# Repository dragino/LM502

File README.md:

# LM502 Project (Base on ASR6502 SX1262 module)
===============

Directory:
- Hardware: LM502 Demo Board Hardware Source, Design in Eagle.
- Software: LM502 Source Code.
- Release: Hex file release
- Miscellaneous: Releated stuff in examples

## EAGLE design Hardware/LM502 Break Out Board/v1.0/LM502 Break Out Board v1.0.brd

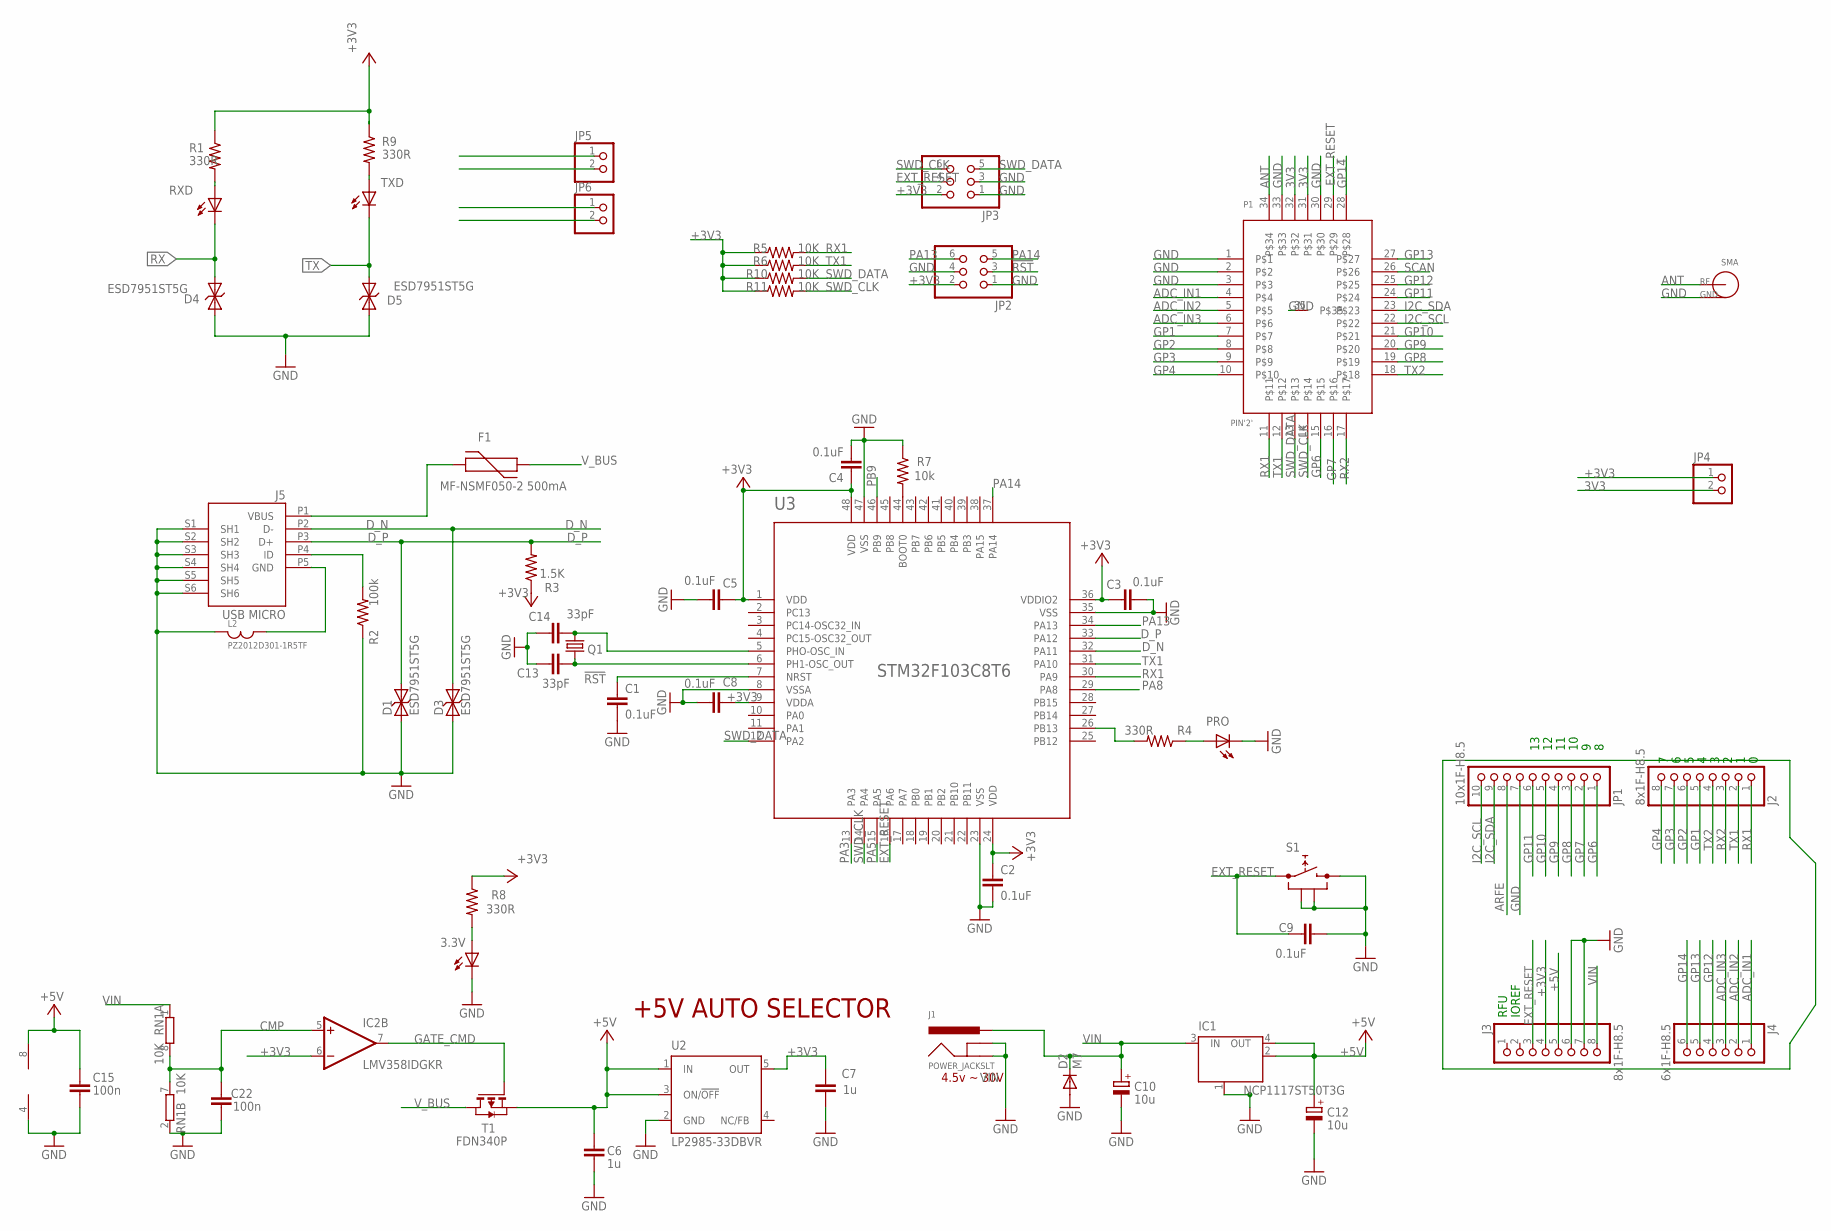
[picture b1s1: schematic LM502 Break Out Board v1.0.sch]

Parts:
3.3V: LEDCHIP-LED0603; CHIP-LED0603
C1, C2, C3, C4, C5, C8, C9: 0.1uF; C0402
C6, C7: 1u; C0603-ROUND
C10, C12: 10u; SMC_B
C13, C14: 33pF; C0402
C15, C22: 100n; C0402
D1, D3, D4, D5: ESD7951ST5G; SOD−923
D2: M7; SMB
F1: MF-NSMF050-2 500mA; R1206
IC1: NCP1117ST50T3G; SOT223
IC2: LMV358IDGKR; MSOP08
J1: POWER_JACKSLT; POWER_JACK_SLOT
J2, J3: 8x1F-H8.5; 1X08
J4: 6x1F-H8.5; 1X06
J5: USB MICRO; CON2_USB_MICRO_B_AT
JP1: 10x1F-H8.5; 1X10
JP2: PINHD-2X3; 2X3-2.0
JP3: PINHD-2X3'2'; 2X03
JP4, JP5, JP6: PINHD-1X2; 1X02
L2: PZ2012D301-1R5TF; C0805@1
P1: PIN'2'; LM502
PRO: LEDCHIP-LED0603; CHIP-LED0603
Q1: CRYSTALHC49S; HC49/S
R1, R4, R8, R9: 330R; R0402
R2: 100k; R0402
R3: 1.5K; R0402
R5, R6, R10, R11: 10K; R0402
R7: 10k; R0402
RN1: 10K; CAY16
RXD: LEDCHIP-LED0603; CHIP-LED0603
S1: PUSH_SWITCH; SWITCH_6X6X5
SMA: SMA-KWE
T1: FDN340P; SOT-23
TXD: LEDCHIP-LED0603; CHIP-LED0603
U2: LP2985-33DBVR; SOT23-DBV
U3: STM32F103C8T6; LQFP48

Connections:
3V3: JP4.2, P1.31, P1.32
!RST: C1.1, JP2.3, U3.7 (NRST)
+3V3: C2.1, C3.1, C4.1, C5.1, C7.2, C8.1, IC2.6 (-IN), J3.4, JP2.2, JP3.2, JP4.1, R1.1, R3.1, R5.1, R6.1, R8.1, R9.1, R10.1, R11.1, U2.5 (OUT), U3.1 (VDD), U3.9 (VDDA), U3.24 (VDD), U3.36 (VDDIO2), U3.48 (VDD)
+5V: C6.2, C12.+, C15.1, IC1.2 (OUT), IC1.4 (OUT), IC2.8 (V+), J3.5, T1.2 (S), U2.1 (IN), U2.3 (ON/!OFF)
ADC_IN1: J4.1, P1.4
ADC_IN2: J4.2, P1.5
ADC_IN3: J4.3, P1.6
ANT: P1.34, SMA.1 (SIG)
ARFE: JP1.8
CMP: C22.2, IC2.5 (+IN), RN1.7 (2), RN1.8 (2)
D_N: D3.P$2 (2), J5.P2 (D-), U3.32 (PA11)
D_P: D1.P$2 (2), J5.P3 (D+), R3.2, U3.33 (PA12)
EXT_RESET: C9.1, J3.3, JP3.4, P1.29, S1.1, U3.16 (PA6)
GATE_CMD: IC2.7 (OUT), T1.3 (G)
GND: 3.3V.C, C1.2, C2.2, C3.2, C4.2, C5.2, C6.1, C7.1, C8.2, C9.2, C10.-, C12.-, C13.1, C14.1, C15.2, C22.1, D1.P$1 (1), D2.A, D3.P$1 (1), D4.P$1 (1), D5.P$1 (1), IC1.1 (GND/ADJ), IC2.4 (V-), J1.GND@1 (GNDBREAK), J1.GND@2 (GND), J3.6, J3.7, J5.S1 (SH1), J5.S2 (SH2), J5.S3 (SH3), J5.S4 (SH4), J5.S5 (SH5), J5.S6 (SH6), JP1.7, JP2.1, JP2.4, JP3.1, JP3.3, L2.1, P1.1, P1.2, P1.3, P1.30, P1.33, P1.35, PRO.C, R2.1, R7.1, RN1.2 (1), S1.2, S1.3, S1.4, SMA.2 (GND), SMA.3 (GND), SMA.4 (GND), SMA.5 (GND), U2.2 (GND), U3.8 (VSSA), U3.23 (VSS), U3.35 (VSS), U3.47 (VSS)
GP1: J2.5, P1.7
GP2: J2.6, P1.8
GP3: J2.7, P1.9
GP4: J2.8, P1.10
GP6: JP1.1, P1.15
GP7: JP1.2, P1.16
GP8: JP1.3, P1.19
GP9: JP1.4, P1.20
GP10: JP1.5, P1.21
GP11: JP1.6, P1.24
GP12: J4.4, P1.25
GP13: J4.5, P1.27
GP14: J4.6, P1.28
I2C_SCL: JP1.10, P1.22
I2C_SDA: JP1.9, P1.23
unnamed: J5.P4 (ID), R2.2
unnamed: F1.2, J5.P1 (VBUS)
unnamed: PRO.A, R4.1
unnamed: R1.2, RXD.A
unnamed: R9.2, TXD.A
unnamed: J5.P5 (GND), L2.2
unnamed: R4.2, U3.26 (PB13)
unnamed: R7.2, U3.44 (BOOT0)
unnamed: C13.2, Q1.1, U3.6 (PH1-OSC_OUT)
unnamed: C14.2, Q1.2, U3.5 (PHO-OSC_IN)
unnamed: 3.3V.A, R8.2
PA3: U3.13 (PA3)
PA5: U3.15 (PA5)
PA8: U3.29 (PA8)
PA13: JP2.6, U3.34 (PA13)
PA14: JP2.5, U3.37 (PA14)
PB9: U3.46 (PB9)
RX: D4.P$2 (2), JP5.1, RXD.C
RX1: J2.1, JP5.2, P1.11, R5.2, U3.30 (PA9)
RX2: J2.3, P1.17
SCAN: P1.26
SWD_CLK: JP3.6, P1.14, R11.2, U3.14 (PA4)
SWD_DATA: JP3.5, P1.13, R10.2, U3.12 (PA2)
TX: D5.P$2 (2), JP6.2, TXD.C
TX1: J2.2, JP6.1, P1.12, R6.2, U3.31 (PA10)
TX2: J2.4, P1.18
VIN: C10.+, D2.C, IC1.3 (IN), J1.PWR, J3.8, RN1.1
V_BUS: F1.1, T1.1 (D)

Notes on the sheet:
IOREF
RFU
+5V AUTO SELECTOR
4.5v ~ 30V

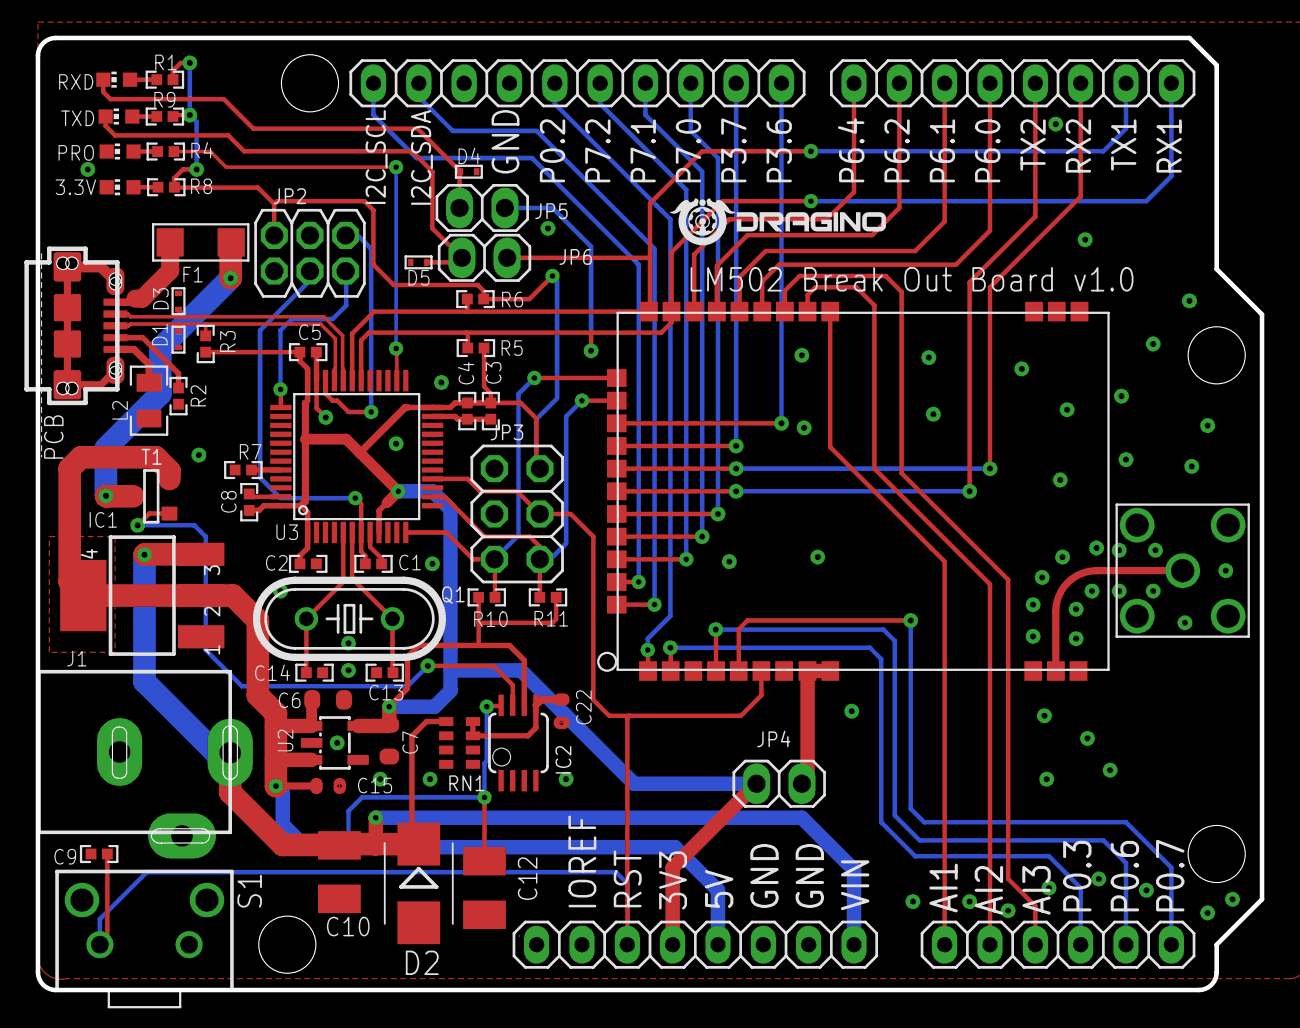
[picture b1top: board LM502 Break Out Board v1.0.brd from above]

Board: 2 copper layers, 68.6 x 53.3 mm, 59 parts (0 on the bottom side), 52 nets.

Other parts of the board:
U$7: LOGO-DRAGINO-2018

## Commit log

2019-09-07 Initiate.
2020-03-06 `vallen` is verified to be less than `len`, therefore, it can never be the case that `vallen >= len + sizeof(rhostname)`.
    This PR fixes the check so the `rhostname` array does not overflow.
    Reported-by: Github Security Lab <securitylab@github.com>
